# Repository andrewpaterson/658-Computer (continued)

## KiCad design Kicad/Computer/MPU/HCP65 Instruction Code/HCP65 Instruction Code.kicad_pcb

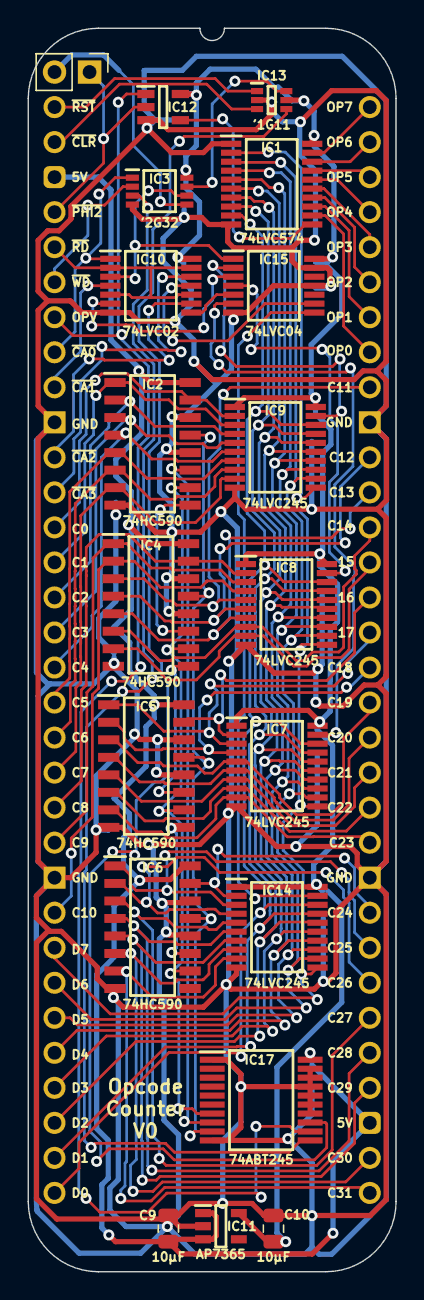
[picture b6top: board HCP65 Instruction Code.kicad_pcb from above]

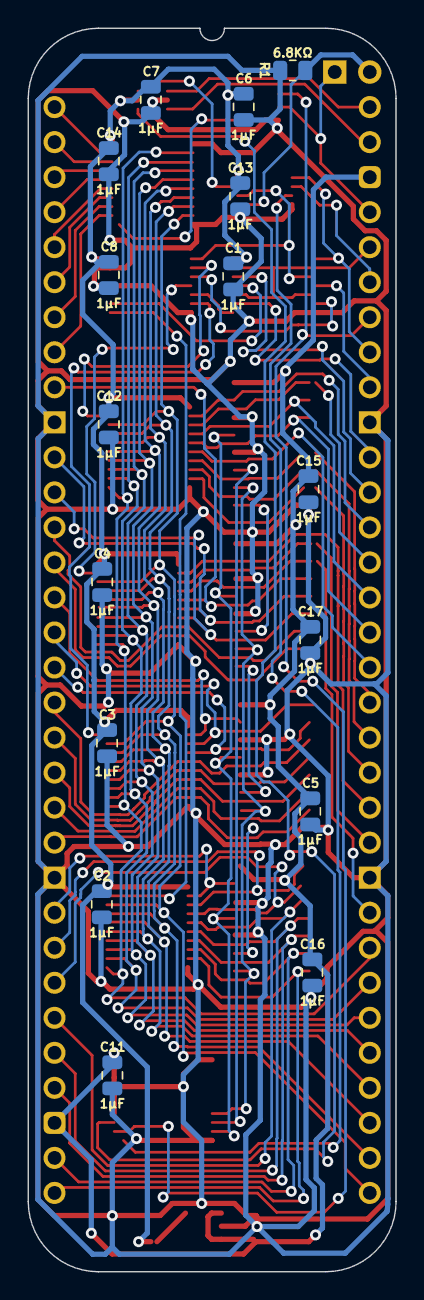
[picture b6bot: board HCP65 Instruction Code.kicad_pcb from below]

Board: 2 copper layers, 26.7 x 90.2 mm, 38 parts (18 on the bottom side), 80 nets.

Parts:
C1, C2, C3, C4, C5, C6, C7, C8, C11, C12, C13, C14, C15, C16, C17: 1μF; C_0805
C9, C10: 10μF; C_0805
IC1: 74LVC574APW,118; SOP65P640X110-20N
IC2, IC4, IC5, IC6: 74HC590D,118; SOIC127P600X175-16N
IC3: 74LVC2G32DP,125; SOP65P400X110-8N
IC7, IC8, IC9, IC14: 74LVC245AT20; SOP65P640X120-20N
IC10: 74LVC02APW,118; SOP65P640X110-14N
IC11: AP7365-33WG-7; SOT95P285X130-5N
IC12: 74LVC1G08GV,125; SOT95P275X110-5N
IC13: 74LVC1G11GW-Q100H; SOP65P210X110-6N
IC15: 74LVC04APW,118; SOP65P640X110-14N
IC17: SN74ABT245BDBR; SOP65P780X200-20N
J1, J3: Pin_Header_01x32; PinHeader_1x32_P2.54mm_Vertical
J2: Conn_02x32_Counter_Clockwise; DIP-64_Board_W22.86mm
J4: Conn_01x02_Pin; PinHeader_1x02_P2.54mm_Vertical
R1: 6.8KΩ; R_0805

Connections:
/3.3V: C1.2, C2.2, C3.2, C4.2, C6.2, C7.2, C8.2, C10.1, C12.2, C13.2, C14.2, IC1.20 (3V), IC3.8 (VCC), IC7.1 (DIR), IC7.20 (3V), IC8.1 (DIR), IC8.20 (3V), IC9.1 (DIR), IC9.20 (3V), IC10.14 (3V), IC11.5 (3.3VOut), IC12.5 (3V), IC13.5 (3V), IC14.1 (DIR), IC14.20 (3V), IC15.14 (3V)
/5V: C5.2, C9.1, C11.2, C15.2, C16.2, C17.2, IC2.16 (VCC), IC4.16 (VCC), IC5.16 (VCC), IC6.16 (VCC), IC11.1 (6VIn), IC11.3 (EN), IC17.20 (5V), J2.3, J2.35
/C0: IC2.15 (Q0), IC9.2 (A0), J2.13
/C1: IC2.1 (Q1), IC9.3 (A1), J2.14
/C2: IC2.2 (Q2), IC9.4 (A2), J2.15
/C3: IC2.3 (Q3), IC9.5 (A3), J2.16
/C4: IC2.4 (Q4), IC9.6 (A4), J2.17
/C5: IC2.5 (Q5), IC9.7 (A5), J2.18
/C6: IC2.6 (Q6), IC9.8 (A6), J2.19
/C7: IC2.7 (Q7), IC9.9 (A7), J2.20
/C8: IC4.15 (Q0), IC8.2 (A0), J2.21
/C9: IC4.1 (Q1), IC8.3 (A1), J2.22
/C10: IC4.2 (Q2), IC8.4 (A2), J2.24
/C11: IC4.3 (Q3), IC8.5 (A3), J2.56
/C12: IC4.4 (Q4), IC8.6 (A4), J2.54
/C13: IC4.5 (Q5), IC8.7 (A5), J2.53
/C14: IC4.6 (Q6), IC8.8 (A6), J2.52
/C15: IC4.7 (Q7), IC8.9 (A7), J2.51
/C16: IC5.15 (Q0), IC7.2 (A0), J2.50
/C17: IC5.1 (Q1), IC7.3 (A1), J2.49
/C18: IC5.2 (Q2), IC7.4 (A2), J2.48
/C19: IC5.3 (Q3), IC7.5 (A3), J2.47
/C20: IC5.4 (Q4), IC7.6 (A4), J2.46
/C21: IC5.5 (Q5), IC7.7 (A5), J2.45
/C22: IC5.6 (Q6), IC7.8 (A6), J2.44
/C23: IC5.7 (Q7), IC7.9 (A7), J2.43
/C24: IC6.15 (Q0), IC14.2 (A0), J2.41
/C25: IC6.1 (Q1), IC14.3 (A1), J2.40
/C26: IC6.2 (Q2), IC14.4 (A2), J2.39
/C27: IC6.3 (Q3), IC14.5 (A3), J2.38
/C28: IC6.4 (Q4), IC14.6 (A4), J2.37
/C29: IC6.5 (Q5), IC14.7 (A5), J2.36
/C30: IC6.6 (Q6), IC14.8 (A6), J2.34
/C31: IC6.7 (Q7), IC14.9 (A7), J2.33
/D0: IC1.9 (D7), IC7.18 (B0), IC8.18 (B0), IC9.18 (B0), IC14.18 (B0), J2.32
/D1: IC1.8 (D6), IC7.17 (B1), IC8.17 (B1), IC9.17 (B1), IC14.17 (B1), J2.31
/D2: IC1.7 (D5), IC7.16 (B2), IC8.16 (B2), IC9.16 (B2), IC14.16 (B2), J2.30
/D3: IC1.6 (D4), IC7.15 (B3), IC8.15 (B3), IC9.15 (B3), IC14.15 (B3), J2.29
/D4: IC1.5 (D3), IC7.14 (B4), IC8.14 (B4), IC9.14 (B4), IC14.14 (B4), J2.28
/D5: IC1.4 (D2), IC7.13 (B5), IC8.13 (B5), IC9.13 (B5), IC14.13 (B5), J2.27
/D6: IC1.3 (D1), IC7.12 (B6), IC8.12 (B6), IC9.12 (B6), IC14.12 (B6), J2.26
/D7: IC1.2 (D0), IC7.11 (B7), IC8.11 (B7), IC9.11 (B7), IC14.11 (B7), J2.25
/GND: C1.1, C2.1, C3.1, C4.1, C5.1, C6.1, C7.1, C8.1, C9.2, C10.2, C11.1, C12.1, C13.1, C14.1, C15.1, C16.1, C17.1, IC1.1 (~OE), IC1.10 (GND), IC2.8 (GND), IC2.12 (~CE), IC2.14 (~OE), IC3.4 (GND), IC4.8 (GND), IC4.12 (~CE), IC4.14 (~OE), IC5.8 (GND), IC5.12 (~CE), IC5.14 (~OE), IC6.8 (GND), IC6.12 (~CE), IC6.14 (~OE), IC7.10 (GND), IC8.10 (GND), IC9.10 (GND), IC10.7 (GND), IC11.2 (GND), IC12.3 (GND), IC13.2 (GND), IC14.10 (GND), IC15.7 (GND), IC15.11 (5A), IC15.13 (6A), IC17.1 (DIR), IC17.10 (GND), IC17.14 (B4), IC17.15 (B3), IC17.16 (B2), IC17.17 (B1), IC17.18 (B0), IC17.19 (~OE), J2.10, J2.23, J2.42, J2.55, R1.2
/OP0: IC1.12 (Q7), J2.57
/OP1: IC1.13 (Q6), J2.58
/OP2: IC1.14 (Q5), J2.59
/OP3: IC1.15 (Q4), J2.60
/OP4: IC1.16 (Q3), J2.61
/OP5: IC1.17 (Q2), J2.62
/OP6: IC1.18 (Q1), J2.63
/OP7: IC1.19 (Q0), J2.64
/Opcode Valid: IC12.1 (B), IC17.12 (B6), J2.7
/Opcode Valid_{5V}: IC2.11 (CPC), IC17.8 (A6)
/Read Count Access_{0T}: IC3.6 (2B), IC10.3 (1Y), IC15.1 (1A)
/Read Count Access_{0}: IC3.3 (2Y), IC17.11 (B7)
/Read Count Access_{1}: IC10.6 (2Y), IC15.3 (2A)
/Read Count Access_{2}: IC10.8 (3Y), IC15.5 (3A)
/Read Count Access_{3}: IC10.11 (4Y), IC15.9 (4A)
/Read Count_{5V}: IC2.13 (CPR), IC4.13 (CPR), IC5.13 (CPR), IC6.13 (CPR), IC17.9 (A7)
/~Clear Counter: IC13.3 (B), J2.2
/~Count Access_{0}: IC3.1 (1A), IC10.1 (1A), J2.8
/~Count Access_{1}: IC10.4 (2A), J2.9
/~Count Access_{2}: IC10.9 (3A), J2.11
/~Count Access_{3}: IC10.12 (4A), J2.12
/~MRC: IC13.4 (Y), IC17.13 (B5)
/~MRC_{5V}: IC2.10 (~MRC), IC4.10 (~MRC), IC5.10 (~MRC), IC6.10 (~MRC), IC17.7 (A5)
/~PHI2: IC12.2 (A), J2.4, J4.1
/~RD: IC10.2 (1B), IC10.5 (2B), IC10.10 (3B), IC10.13 (4B), J2.5
/~Read Count Access_{0}: IC9.19 (~OE), IC15.2 (1Y)
/~Read Count Access_{1}: IC8.19 (~OE), IC15.4 (2Y)
/~Read Count Access_{2}: IC7.19 (~OE), IC15.6 (3Y)
/~Read Count Access_{3}: IC14.19 (~OE), IC15.8 (4Y)
/~Reset: IC13.1 (A), J2.1
/~WD: IC3.2 (1B), J2.6
/~Write Count: IC3.7 (1Y), IC13.6 (C)
unnamed: IC1.11 (CP), IC12.4 (Y)
unnamed: IC2.9 (~RCO), IC4.11 (CPC)
unnamed: IC3.5 (2A), J4.2, R1.1
unnamed: IC4.9 (~RCO), IC5.11 (CPC)
unnamed: IC5.9 (~RCO), IC6.11 (CPC)

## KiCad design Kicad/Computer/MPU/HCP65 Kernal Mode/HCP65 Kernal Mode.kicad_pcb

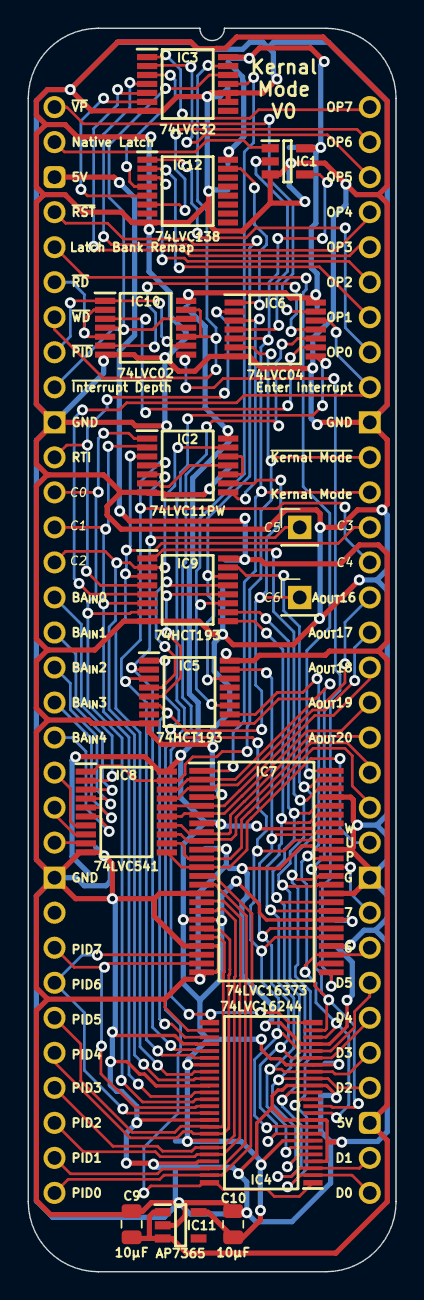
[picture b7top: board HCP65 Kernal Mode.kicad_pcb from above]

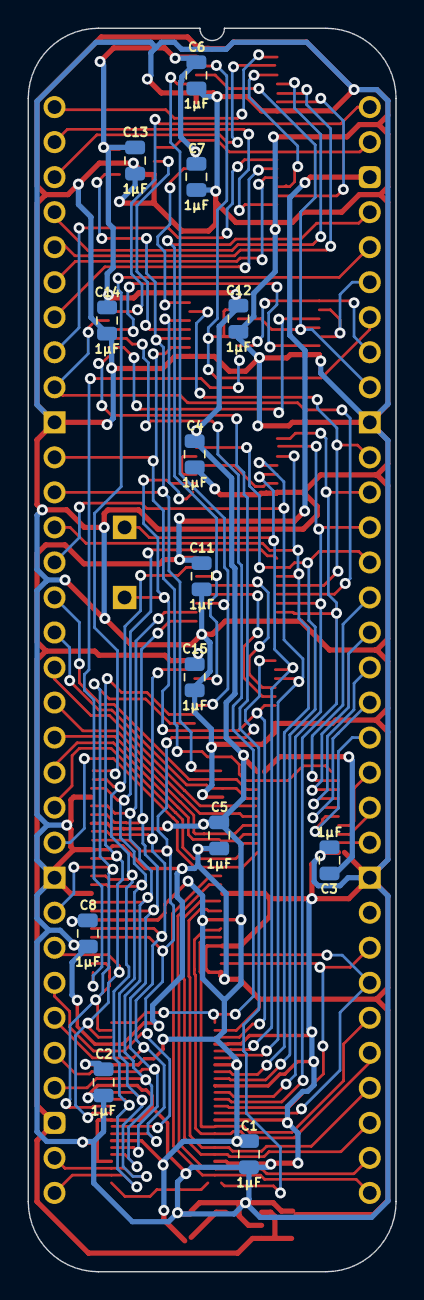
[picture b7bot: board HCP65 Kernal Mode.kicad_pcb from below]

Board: 2 copper layers, 26.7 x 90.2 mm, 32 parts (15 on the bottom side), 77 nets.

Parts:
C1, C2, C3, C4, C5, C6, C7, C8, C11, C12, C13, C14, C15: 1μF; C_0805
C9, C10: 10μF; C_0805
IC1: 74LVC1G02GV,125; SOT95P275X110-5N
IC2: 74LVC11PW,112; SOP65P640X110-14N
IC3: 74LVC32APW,118; SOP65P640X110-14N
IC4: 74LVC16244ADGG,112; 74LVC16244ADGG112
IC5, IC9: 74HCT193PW,118; SOP65P640X110-16N
IC6: 74LVC04APW,118; SOP65P640X110-14N
IC7: 74LVC16373ADL,118; SOP64P1025X280-48N
IC8: 74LVC541APW,118; SOP65P640X110-20N
IC10: 74LVC02APW,118; SOP65P640X110-14N
IC11: AP7365-33WG-7; SOT95P285X130-5N
IC12: 74LVC138APW-Q100J; SOP65P640X110-16N
J1, J3: Pin_Header_01x32; PinHeader_1x32_P2.54mm_Vertical
J2: Conn_02x32_Counter_Clockwise; DIP-64_Board_W22.86mm
TP1, TP2: TestPoint; PinHeader_1x01_P2.54mm_Vertical

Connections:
5V: C9.1, C11.2, C15.2, IC5.16 (5V), IC9.16 (5V), IC11.1 (6VIn), IC11.3 (EN), J2.3, J2.35
/3.3V: C1.2, C2.2, C3.2, C4.2, C5.2, C6.2, C7.2, C8.2, C10.1, C12.2, C13.2, C14.2, IC1.5 (3V), IC2.14 (3V), IC3.14 (3V), IC4.7 (3V), IC4.18 (3V), IC4.31 (3V), IC4.42 (3V), IC6.14 (3V), IC7.7 (3V), IC7.18 (3V), IC7.31 (3V), IC7.42 (3V), IC8.20 (3V), IC10.14 (3V), IC11.5 (3.3VOut), IC12.16 (3V)
/C0·C1·C2: IC2.10 (3B), IC2.12 (1Y)
/C3·C4·C5: IC2.6 (2Y), IC2.11 (3C)
/Kernal Mode_{ PART}: IC2.8 (3Y), IC6.3 (2A)
/Read Interrupt Depth: IC6.11 (5A), IC10.6 (2Y)
/Read Process ID: IC6.9 (4A), IC10.3 (1Y)
/Write Process ID: IC7.25 (2LE), IC10.8 (3Y)
/~Kernal Mode_{ PART}: IC1.2 (A), IC6.4 (2Y)
/~RTI: IC6.1 (1A), IC12.15 (~Y0)
/~Read Interrupt Depth: IC4.24 (4~OE), IC4.25 (3~OE), IC6.10 (5Y)
/~Read Process ID: IC4.1 (1~OE), IC4.48 (2~OE), IC6.8 (4Y)
/~TCD: IC5.4 (CPD), IC9.13 (~TCD)
/~TCU: IC5.5 (CPU), IC9.12 (~TCU)
/~Write Interrupt Depth: IC3.11 (4Y), IC5.11 (~PL), IC9.11 (~PL)
A_{OUT}16: IC7.2 (1Q0), IC8.18 (Y0), J2.50
A_{OUT}17: IC7.3 (1Q1), IC8.17 (Y1), J2.49
A_{OUT}18: IC7.5 (1Q2), IC8.16 (Y2), J2.48
A_{OUT}19: IC7.6 (1Q3), IC8.15 (Y3), J2.47
A_{OUT}20: IC7.8 (1Q4), IC8.14 (Y4), J2.46
A_{OUT}21: IC7.9 (1Q5), IC8.13 (Y5), J2.45
A_{OUT}22: IC7.11 (1Q6), IC8.12 (Y6), J2.44
A_{OUT}23: IC7.12 (1Q7), IC8.11 (Y7), J2.43
BA_{IN}0: IC8.2 (A0), J2.15
BA_{IN}1: IC8.3 (A1), J2.16
BA_{IN}2: IC8.4 (A2), J2.17
BA_{IN}3: IC8.5 (A3), J2.18
BA_{IN}4: IC8.6 (A4), J2.19
BA_{IN}5: IC8.7 (A5), J2.20
BA_{IN}6: IC8.8 (A6), J2.21
BA_{IN}7: IC8.9 (A7), J2.22
C0: IC2.1 (1A), IC4.36 (3A0), IC9.7 (Q3), J2.12
C1: IC2.2 (1B), IC4.35 (3A1), IC9.6 (Q2), J2.13
C2: IC2.13 (1C), IC4.33 (3A2), IC9.2 (Q1), J2.14
C3: IC2.3 (2A), IC4.32 (3A3), IC9.3 (Q0), J2.52
C4: IC2.4 (2B), IC4.30 (4A0), IC5.3 (Q0), J2.51
C5: IC2.5 (2C), IC4.29 (4A1), IC5.2 (Q1), TP2.1
C6: IC2.9 (3A), IC4.27 (4A2), IC5.6 (Q2), TP1.1
D0: IC4.2 (1Y0), IC4.13 (3Y0), IC7.36 (2D0), IC7.47 (1D0), IC9.15 (D0), J2.33
D1: IC4.3 (1Y1), IC4.14 (3Y1), IC7.35 (2D1), IC7.46 (1D1), IC9.1 (D1), J2.34
D2: IC4.5 (1Y2), IC4.16 (3Y2), IC7.33 (2D2), IC7.44 (1D2), IC9.10 (D2), J2.36
D3: IC4.6 (1Y3), IC4.17 (3Y3), IC7.32 (2D3), IC7.43 (1D3), IC9.9 (D3), J2.37
D4: IC4.8 (2Y0), IC4.19 (4Y0), IC5.15 (D0), IC7.30 (2D4), IC7.41 (1D4), J2.38
D5: IC4.9 (2Y1), IC4.20 (4Y1), IC5.1 (D1), IC7.29 (2D5), IC7.40 (1D5), J2.39
D6: IC4.11 (2Y2), IC4.22 (4Y2), IC5.10 (D2), IC7.27 (2D6), IC7.38 (1D6), J2.40
D7: IC4.12 (2Y3), IC4.23 (4Y3), IC5.9 (D3), IC7.26 (2D7), IC7.37 (1D7), J2.41
Enter Interrupt: IC6.12 (6Y), IC9.5 (CPU), J2.56
GND: C1.1, C2.1, C3.1, C4.1, C5.1, C6.1, C7.1, C8.1, C9.2, C10.2, C11.1, C12.1, C13.1, C14.1, C15.1, IC1.3 (GND), IC2.7 (GND), IC3.7 (GND), IC3.9 (3A), IC3.10 (3B), IC4.4 (GND), IC4.10 (GND), IC4.15 (GND), IC4.21 (GND), IC4.26 (4A3), IC4.28 (GND), IC4.34 (GND), IC4.39 (GND), IC4.45 (GND), IC5.8 (GND), IC6.7 (GND), IC7.4 (GND), IC7.10 (GND), IC7.15 (GND), IC7.21 (GND), IC7.24 (2~OE), IC7.28 (GND), IC7.34 (GND), IC7.39 (GND), IC7.45 (GND), IC8.10 (GND), IC9.8 (GND), IC10.7 (GND), IC11.2 (GND), IC12.8 (GND), J2.10, J2.23, J2.42, J2.55
Kernal Mode: IC1.4 (Y), IC6.5 (3A), IC7.1 (1~OE), J2.53
Latch Bank Remap: IC7.48 (1LE), J2.5
Native Latch: IC1.1 (B), J2.2
unnamed: IC3.3 (1Y), IC12.4 (~E1)
unnamed: IC3.6 (2Y), IC12.5 (~E2)
OP0: IC12.1 (A0), J2.57
OP1: IC12.2 (A1), J2.58
OP2: IC12.3 (A2), J2.59
OP3: IC3.5 (2B), J2.60
OP4: IC3.4 (2A), J2.61
OP5: IC3.2 (1B), J2.62
OP6: IC12.6 (E3), J2.63
OP7: IC3.1 (1A), J2.64
PID0: IC4.47 (1A0), IC7.13 (2Q0), J2.32
PID1: IC4.46 (1A1), IC7.14 (2Q1), J2.31
PID2: IC4.44 (1A2), IC7.16 (2Q2), J2.30
PID3: IC4.43 (1A3), IC7.17 (2Q3), J2.29
PID4: IC4.41 (2A0), IC7.19 (2Q4), J2.28
PID5: IC4.40 (2A1), IC7.20 (2Q5), J2.27
PID6: IC4.38 (2A2), IC7.22 (2Q6), J2.26
PID7: IC4.37 (2A3), IC7.23 (2Q7), J2.25
RTI: IC6.2 (1Y), IC9.4 (CPD), J2.11
~Interrupt Depth: IC3.12 (4A), IC10.4 (2A), IC10.12 (4A), J2.9
~Kernal Mode: IC6.6 (3Y), IC8.1 (~OE1), IC8.19 (~OE2), J2.54
~Process ID: IC10.1 (1A), IC10.9 (3A), J2.8
~RD: IC10.2 (1B), IC10.5 (2B), J2.6
~Reset: IC5.14 (MR), IC9.14 (MR), J2.4
~VP: IC6.13 (6A), J2.1
~WD: IC3.13 (4B), IC10.10 (3B), IC10.13 (4B), J2.7
